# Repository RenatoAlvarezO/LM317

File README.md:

#   Fuente Regulable 

Una fuente regulable simple, con el Circuito Integrado LM317, que está diseñado para un rango de 1,25V - 28V.

El proyecto fue desarrollado en KiCAD.

Por el momento solo está el esquema, en los proximos días se agregará el diseño de la PCB.

#   Diseño

El diseño de esta fuente está basado en el punto 9.2 de la hoja de datos https://www.ti.com/lit/ds/symlink/lm317.pdf con algunas modificaciones:

-   Se agregó un LED en la entrada para señalización
-   Existe un punto en la entrada para alimentación de otros dispositivos como instrumentos de medición.

Hay que tener en cuenta, que el disipador para el LM317 no se encuentra en el esquema, pero es imperativo colocar uno, ya que al usar toda su potencia, puede llegar a calentarse bastante.

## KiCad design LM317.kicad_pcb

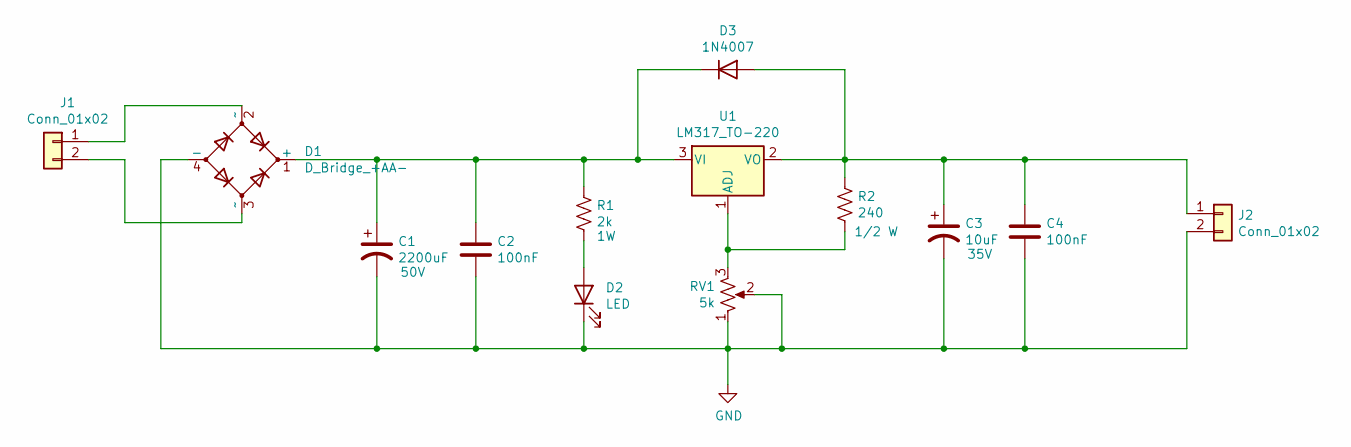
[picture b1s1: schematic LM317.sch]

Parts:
C1: 2200uF; CP_Radial_D14.0mm_P7.50mm
C2, C4: 100nF; C_Disc_D7.5mm_W2.5mm_P5.00mm
C3: 10uF; CP_Radial_D7.5mm_P2.50mm; Voltage 35V
D1: D_Bridge_+AA-; Diode_Bridge_Vishay_KBL
D2: LED; LED_D5.0mm
D3: 1N4007; D_DO-41_SOD81_P10.16mm_Horizontal
J1, J2: Conn_01x02; TerminalBlock_bornier-2_P5.08mm
R1: 2k; R_Axial_DIN0207_L6.3mm_D2.5mm_P15.24mm_Horizontal
R2: 240; R_Axial_DIN0204_L3.6mm_D1.6mm_P7.62mm_Horizontal
RV1: 5k; Potentiometer_Alps_RK163_Single_Horizontal
U1: LM317_TO-220; TO-220-3_Vertical

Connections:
ENTRADA: C1.1, C2.1, D1.1 (+), D3.1 (K), R1.1, U1.3 (VI); also elsewhere on the board
GND: C1.2, C2.2, C3.2, C4.2, D1.4 (-), D2.1 (K), J2.2, RV1.1, RV1.2; also elsewhere on the board
unnamed: D1.2 (~~), J1.1
unnamed: D1.3 (~~), J1.2
unnamed: D2.2 (A), R1.2
unnamed: R2.2, RV1.3, U1.1 (ADJ)
SALIDA: C3.1, C4.1, D3.2 (A), J2.1, R2.1, U1.2 (VO); also elsewhere on the board

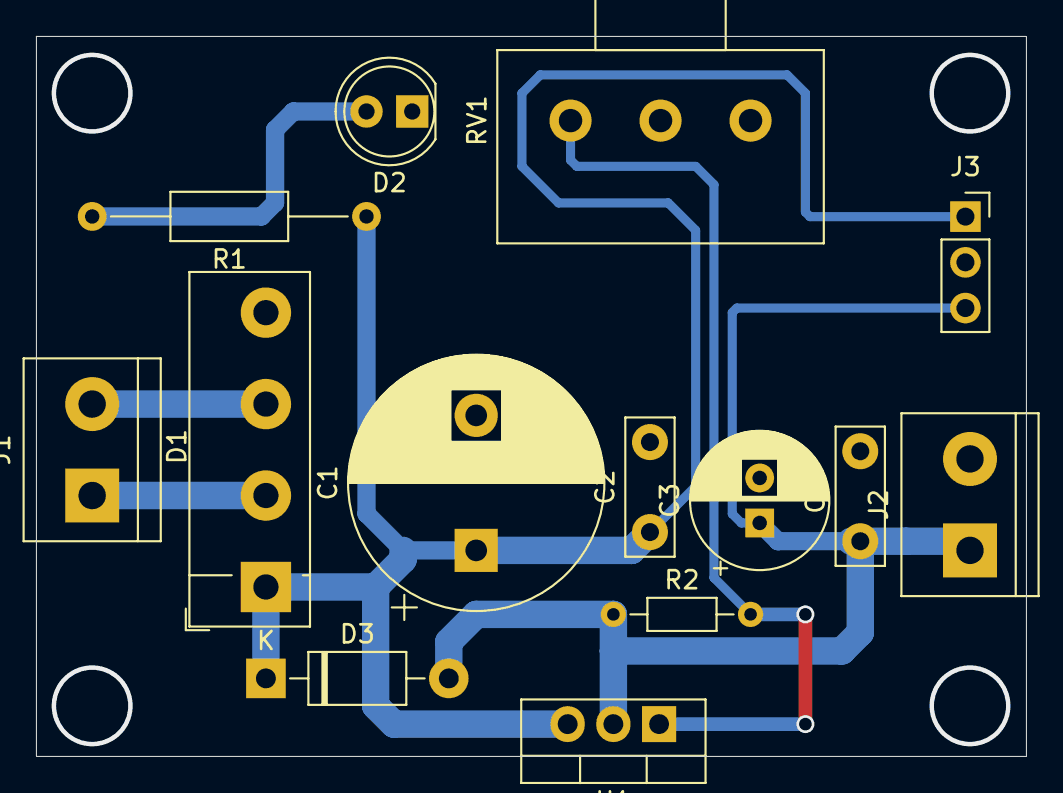
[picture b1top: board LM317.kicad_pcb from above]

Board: 2 copper layers, 55.0 x 40.0 mm, 14 parts (0 on the bottom side), 7 nets.

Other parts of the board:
J3: Conn_01x03; PinSocket_1x03_P2.54mm_Vertical

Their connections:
ENTRADA: J3.1; also elsewhere on the board
GND: J3.2; also elsewhere on the board
SALIDA: J3.3; also elsewhere on the board

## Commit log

2020-10-10 Sin PCB
2020-10-10 PCB Pendiente
2020-10-10 Falta PCB
2020-10-19 PCB Completa con Voltimetro
